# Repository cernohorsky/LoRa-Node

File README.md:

# LoRa Node

Simple, cheap, very small size Lora node with PCB antenna on 868 MHz. Compatible with FT232RL FTDI USB To TTL Serial Converter. Design includes lot of free GPIO's, push button and LED.

It's necessary to <b>burn bootloader with ISP before RFM95W module is soldered</b>.

<b>Schematic</b>

<b> S11 Measurement </b>

<b> Sleep current measurement </b>

Based on: http://www.ti.com/lit/an/swra228c/swra228c.pdf

#RFM95W, #ATMEGA328P, #arduino, #lora, #pcb antenna, #inverted f antenna

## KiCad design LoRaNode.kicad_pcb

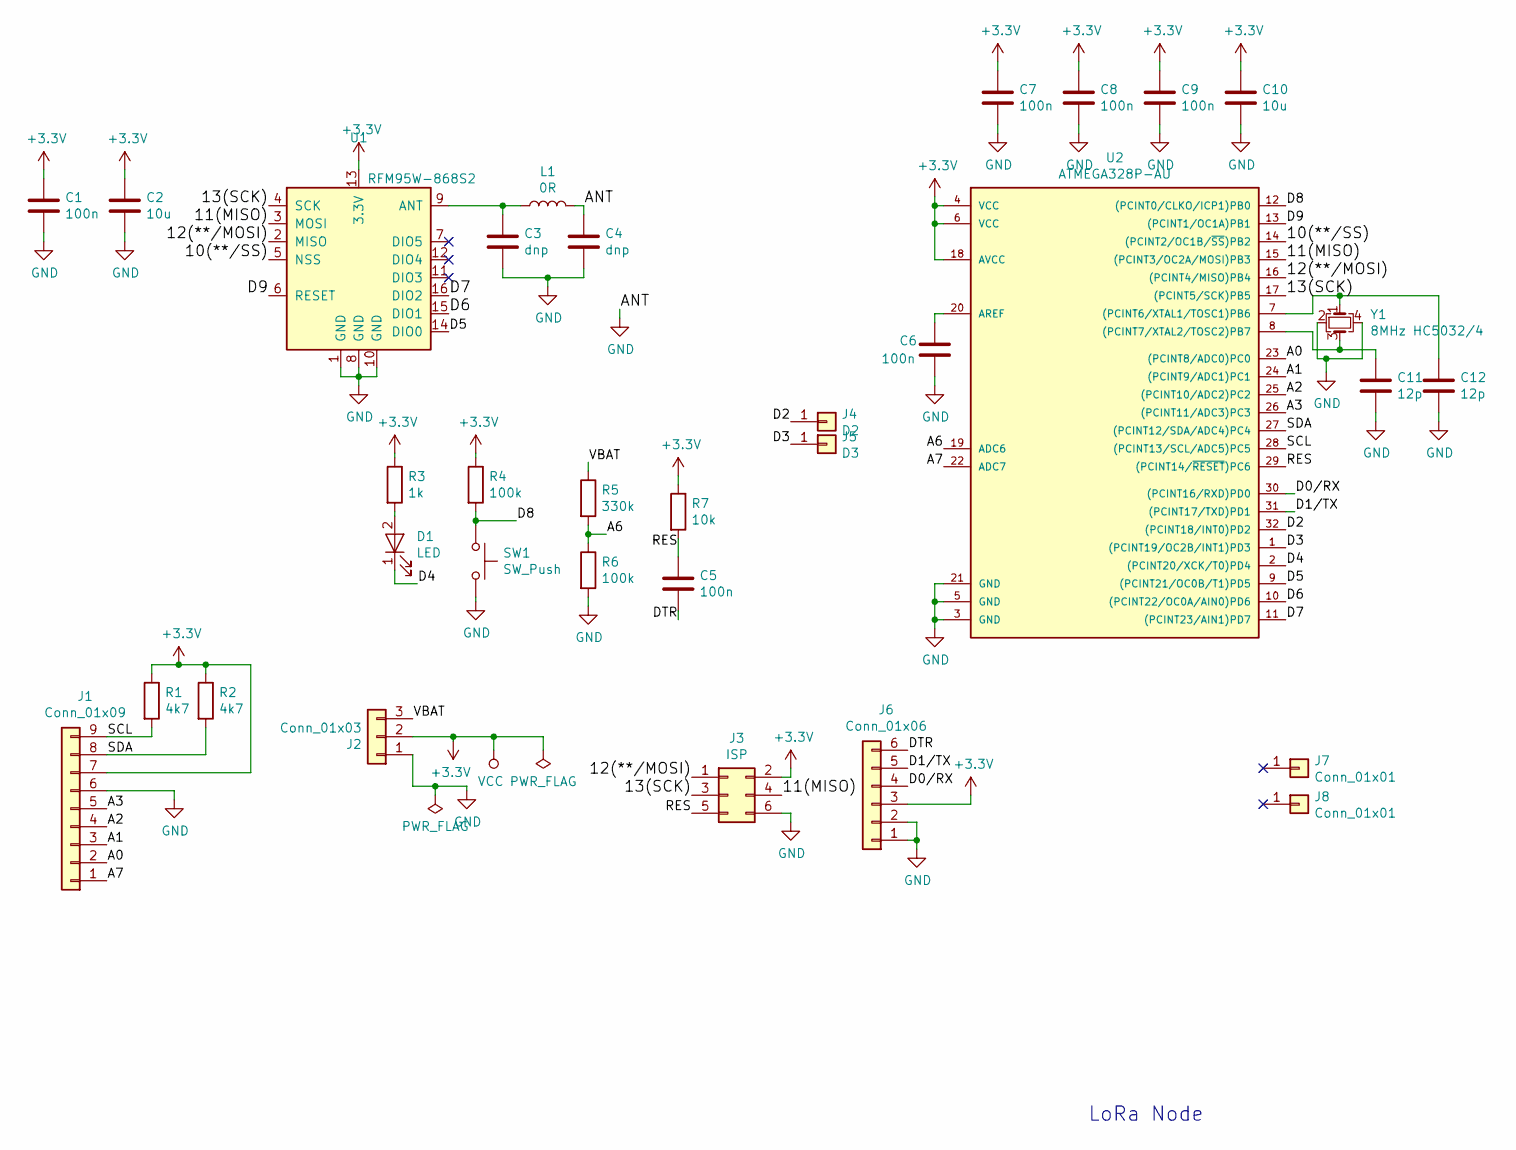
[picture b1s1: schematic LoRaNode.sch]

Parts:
C1, C5, C6, C7, C8, C9: 100n; C_0603_1608Metric
C2, C10: 10u; C_0805_2012Metric
C3, C4: dnp; C_0402_1005Metric
C11, C12: 12p; C_0603_1608Metric
D1: LED; LED_1206_3216Metric
J1: Conn_01x09; PinSocket_1x09_P2.54mm_Vertical
J2: Conn_01x03; PinHeader_1x03_P2.54mm_Vertical
J3: ISP; Pin_Header_Straight_2x03_Pitch2.54mm
J4: D2; TestPoint_Pad_D1.0mm
J5: D3; TestPoint_Pad_D1.0mm
J6: Conn_01x06; Pin_Header_Straight_1x06_Pitch2.54mm
J7, J8: Conn_01x01; MountingHole_2.2mm_M2
L1: 0R; L_0402_1005Metric
R1, R2: 4k7; R_0603_1608Metric
R3: 1k; R_0603_1608Metric
R4, R6: 100k; R_0603_1608Metric
R5: 330k; R_0603_1608Metric
R7: 10k; R_0603_1608Metric
SW1: SW_Push; SMD-PushButton-6x3.6mm
U1: RFM95W-868S2; HOPERF_RFM95W_SMD
U2: ATMEGA328P-AU; TQFP-32_7x7mm_P0.8mm
Y1: 8MHz HC5032/4; Crystal_SMD_5032-4pin_5.0x3.2mm

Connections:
+3V3: C1.1, C2.1, C7.1, C8.1, C9.1, C10.1, J1.7, J2.2, J3.2, J6.3, R1.1, R2.1, R3.1, R4.1, R7.1, U1.13 (3.3V), U2.4 (VCC), U2.6 (VCC), U2.18 (AVCC)
/10(**/SS): U1.5 (NSS), U2.14 ((PCINT2/OC1B/~SS~)PB2)
/11(MISO): J3.4, U1.3 (MOSI), U2.15 ((PCINT3/OC2A/MOSI)PB3)
/12(**/MOSI): J3.1, U1.2 (MISO), U2.16 ((PCINT4/MISO)PB4)
/13(SCK): J3.3, U1.4 (SCK), U2.17 ((PCINT5/SCK)PB5)
/A0: J1.2, U2.23 ((PCINT8/ADC0)PC0)
/A1: J1.3, U2.24 ((PCINT9/ADC1)PC1)
/A2: J1.4, U2.25 ((PCINT10/ADC2)PC2)
/A3: J1.5, U2.26 ((PCINT11/ADC3)PC3)
/A6: R5.2, R6.1, U2.19 (ADC6)
/A7: J1.1, U2.22 (ADC7)
/D0/RX: J6.4, U2.30 ((PCINT16/RXD)PD0)
/D1/TX: J6.5, U2.31 ((PCINT17/TXD)PD1)
/D2: J4.1, U2.32 ((PCINT18/INT0)PD2)
/D3: J5.1, U2.1 ((PCINT19/OC2B/INT1)PD3)
/D4: D1.1 (K), U2.2 ((PCINT20/XCK/T0)PD4)
/D5: U1.14 (DIO0), U2.9 ((PCINT21/OC0B/T1)PD5)
/D6: U1.15 (DIO1), U2.10 ((PCINT22/OC0A/AIN0)PD6)
/D7: U1.16 (DIO2), U2.11 ((PCINT23/AIN1)PD7)
/D8: R4.2, SW1.1, U2.12 ((PCINT0/CLKO/ICP1)PB0)
/D9: U1.6 (RESET), U2.13 ((PCINT1/OC1A)PB1)
/DTR: C5.2, J6.6
/RES: C5.1, J3.5, R7.2, U2.29 ((PCINT14/~RESET~)PC6)
/SCL: J1.9, R1.2, U2.28 ((PCINT13/SCL/ADC5)PC5)
/SDA: J1.8, R2.2, U2.27 ((PCINT12/SDA/ADC4)PC4)
/VBAT: J2.3, R5.1
GND: C1.2, C2.2, C3.2, C4.1, C4.2, C6.2, C7.2, C8.2, C9.2, C10.2, C11.2, C12.2, J1.6, J2.1, J3.6, J6.1, J6.2, L1.2, R6.2, SW1.2, U1.1 (GND), U1.8 (GND), U1.10 (GND), U2.3 (GND), U2.5 (GND), U2.21 (GND), Y1.2, Y1.4
unnamed: C3.1, L1.1, U1.9 (ANT)
unnamed: C6.1, U2.20 (AREF)
unnamed: C11.1, U2.8 ((PCINT7/XTAL2/TOSC2)PB7), Y1.3
unnamed: C12.1, U2.7 ((PCINT6/XTAL1/TOSC1)PB6), Y1.1
unnamed: D1.2 (A), R3.2

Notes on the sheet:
LoRa Node

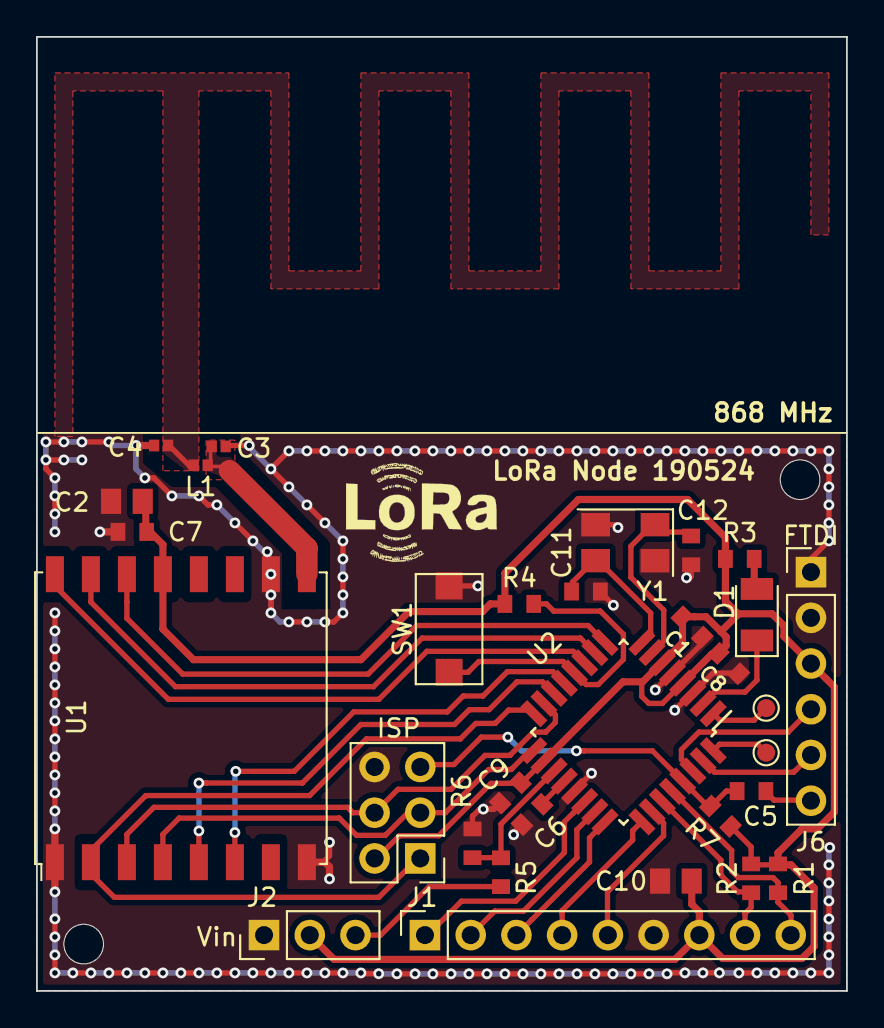
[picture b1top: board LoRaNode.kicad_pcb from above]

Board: 2 copper layers, 45.0 x 53.0 mm, 33 parts (0 on the bottom side), 32 nets.

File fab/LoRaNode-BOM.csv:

Id;Designator;Package;Quantity;Designation;Supplier and ref
17;C1,C6,C7,C8,C9,C5;C_0603_1608Metric;6;100n;
7;C10,C2;C_0805_2012Metric;2;10u;
18;C11,C12;C_0603_1608Metric;2;12p;
16;C3,C4;C_0402_1005Metric;2;dnp;
15;D1;LED_1206_3216Metric;1;LED;
13;J1;PinSocket_1x09_P2.54mm_Vertical;1;Conn_01x09;
9;J2;PinHeader_1x03_P2.54mm_Vertical;1;Conn_01x03;
2;J3;Pin_Header_Straight_2x03_Pitch2.54mm;1;ISP;
3;J6;Pin_Header_Straight_1x06_Pitch2.54mm;1;Conn_01x06;
19;L1;L_0402_1005Metric;1;0R;
21;R1,R2;R_0603_1608Metric;2;4k7;
14;R3;R_0603_1608Metric;1;1k;
5;R5;R_0603_1608Metric;1;330k;
6;R6,R4;R_0603_1608Metric;2;100k;
20;R7;R_0603_1608Metric;1;10k;
11;SW1;SMD-PushButton-6x3.6mm;1;SW_Push;
1;U1;HOPERF_RFM95W_SMD;1;RFM95W-868S2;
22;U2;TQFP-32_7x7mm_P0.8mm;1;ATMEGA328P-AU;
4;Y1;Crystal_SMD_5032-4pin_5.0x3.2mm;1;8MHz HC5032/4;

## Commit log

2019-03-15 v0.1
2019-03-22 Moved I2C and Power connectors, Added antenna test pads, ERC done, DRC done
2019-03-22 Added lib files
2019-03-22 Changed I2C pinout
2019-03-22 Small changes
2019-03-22 PCB manufactured
2019-04-15 S11 Measurement
2019-05-13 Silkscreen correction, removed antenna testing pads
2019-05-13 Added picture
2019-05-17 Added more 5 GPIO's and push button
2019-05-20 Added LED, changed footprints to actual KiCAD library
2019-05-20 Changed RFM95W footprint
2019-05-21 Added mounting holes
2019-05-21 Updated RFM95W 3D model
2019-05-21 Updated schematic
2019-05-22 Anotation reset, added BOM
2019-05-24 Corrected silk layer, removed old footprint files
2019-05-29 Added firmware example
2019-06-02 Added sleep current measurement result
